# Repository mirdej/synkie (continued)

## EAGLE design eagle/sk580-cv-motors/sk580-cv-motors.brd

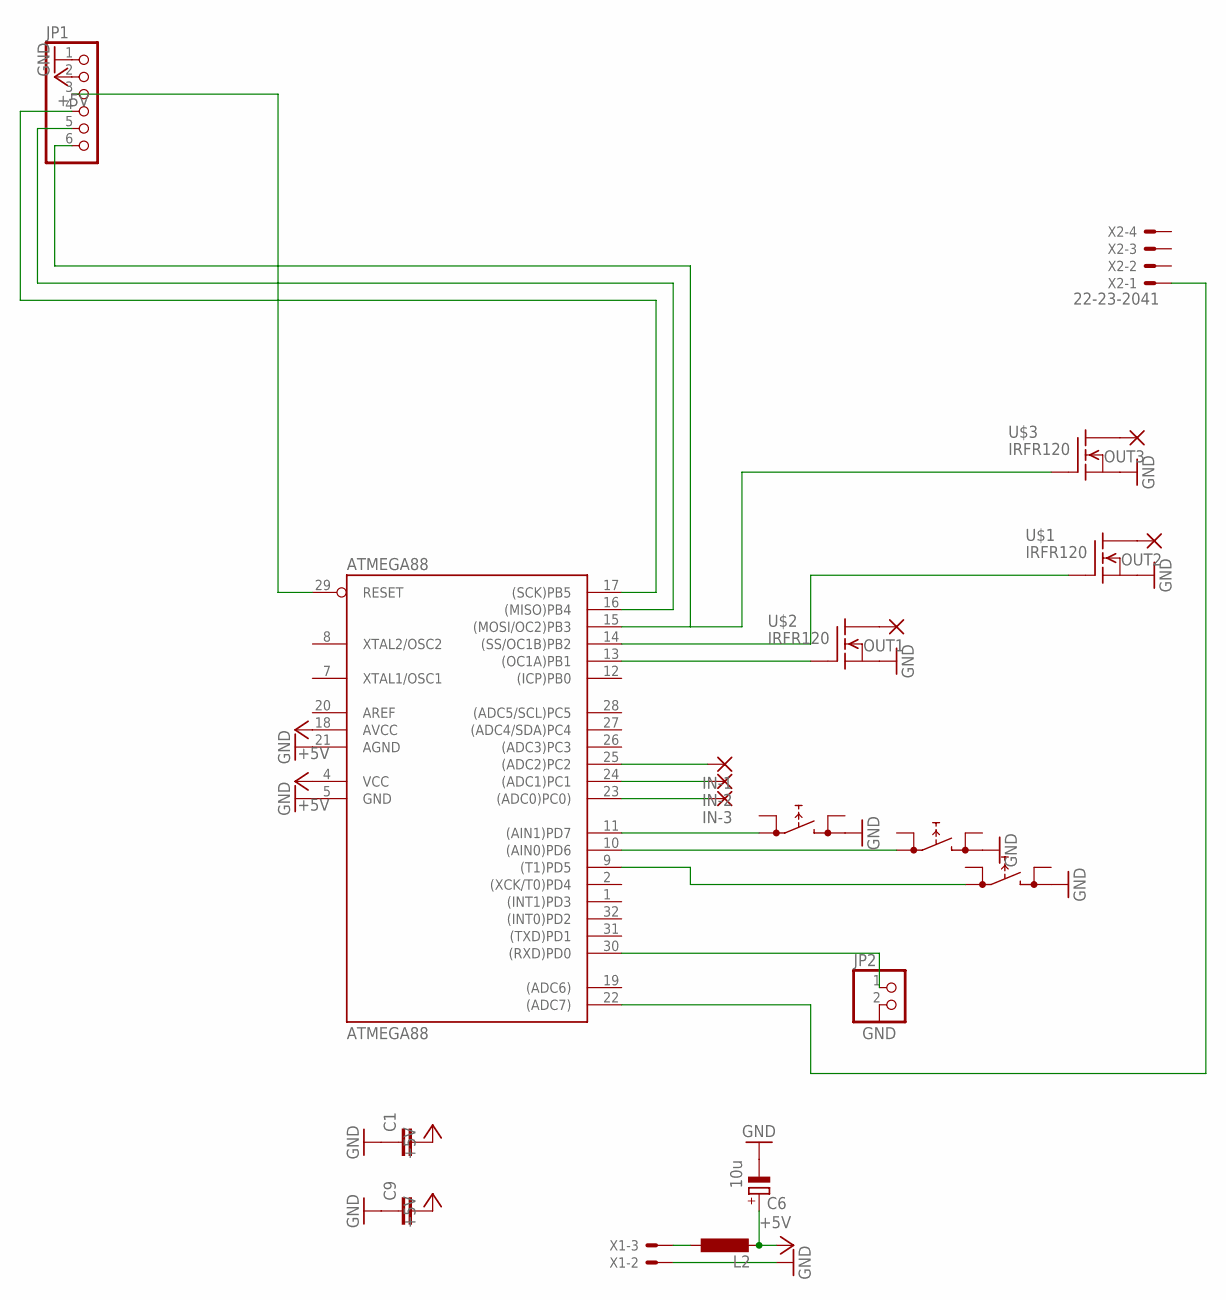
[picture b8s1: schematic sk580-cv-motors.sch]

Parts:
ATMEGA88: ATMEGA88; TQFP32-08
C1, C9: C-EUC0603; C0603
C6: 10u; CT3528
DUB2: PRINTTASTER_SMD; SMD_SWITCH
DUB-1, DUB-3: PRINTTASTER_SMD; SMD_SWITCH
IN-1, IN-2, IN-3: 3,17/1,1
JP1: PINHD-1X6; 1X06
JP2: PINHD-1X2; 1X02
L2: L-EUL5038P; L5038P
OUT1, OUT2, OUT3: 3,17/1,1
U$1, U$2, U$3: IRFR120; DPAK
X1: 22-23-2031
X2: 22-23-2041

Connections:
+5V: ATMEGA88.4 (VCC), ATMEGA88.18 (AVCC), C1.2, C6.+, C9.2, JP1.2, L2.2
AREF: ATMEGA88.20 (AREF)
GND: ATMEGA88.5 (GND), ATMEGA88.21 (AGND), C1.1, C6.-, C9.1, DUB2.BB (1), DUB-1.BB (1), DUB-3.BB (1), JP1.1, JP2.2, U$1.3 (S), U$2.3 (S), U$3.3 (S), X1.2
unnamed: ATMEGA88.29 (RESET), JP1.3
unnamed: ATMEGA88.17 ((SCK)PB5), JP1.4
unnamed: ATMEGA88.16 ((MISO)PB4), JP1.5
unnamed: ATMEGA88.23 ((ADC0)PC0)), IN-3.1
unnamed: ATMEGA88.24 ((ADC1)PC1), IN-2.1
unnamed: ATMEGA88.25 ((ADC2)PC2), IN-1.1
unnamed: ATMEGA88.22 ((ADC7)), X2.1
unnamed: ATMEGA88.30 ((RXD)PD0), JP2.1
unnamed: L2.1, X1.3
unnamed: ATMEGA88.13 ((OC1A)PB1), U$2.1 (G)
unnamed: OUT1.1, U$2.4 (D)
unnamed: ATMEGA88.14 ((SS/OC1B)PB2), U$1.1 (G)
unnamed: OUT2.1, U$1.4 (D)
unnamed: ATMEGA88.15 ((MOSI/OC2)PB3), JP1.6, U$3.1 (G)
unnamed: OUT3.1, U$3.4 (D)
RESET: ATMEGA88.11 ((AIN1)PD7), DUB-1.AA (0)
RESET1: ATMEGA88.10 ((AIN0)PD6), DUB2.AA (0)
RESET2: ATMEGA88.9 ((T1)PD5), DUB-3.AA (0)

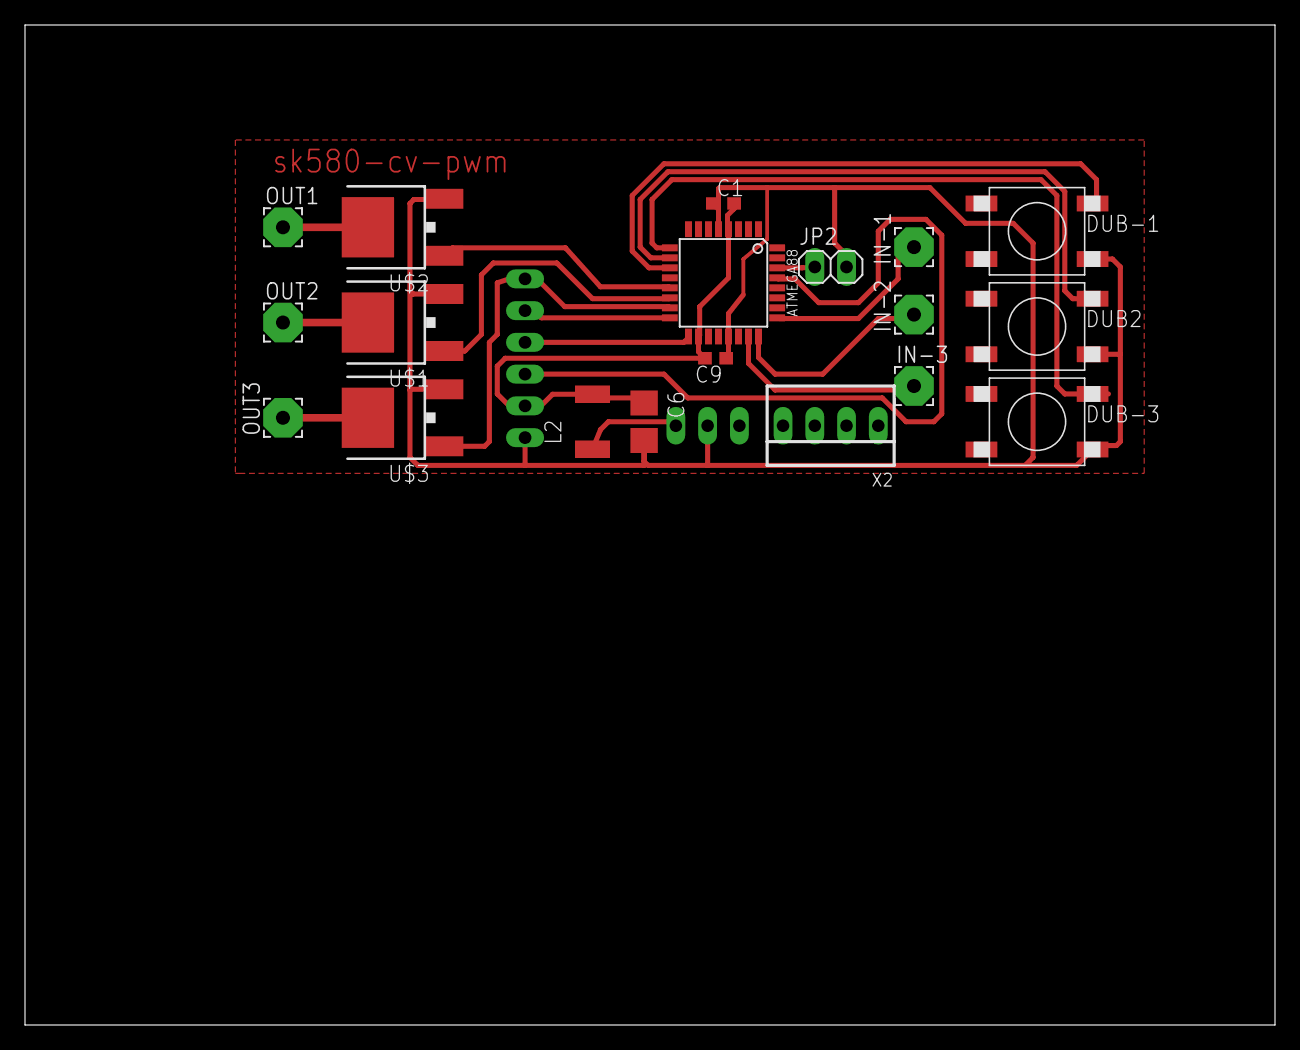
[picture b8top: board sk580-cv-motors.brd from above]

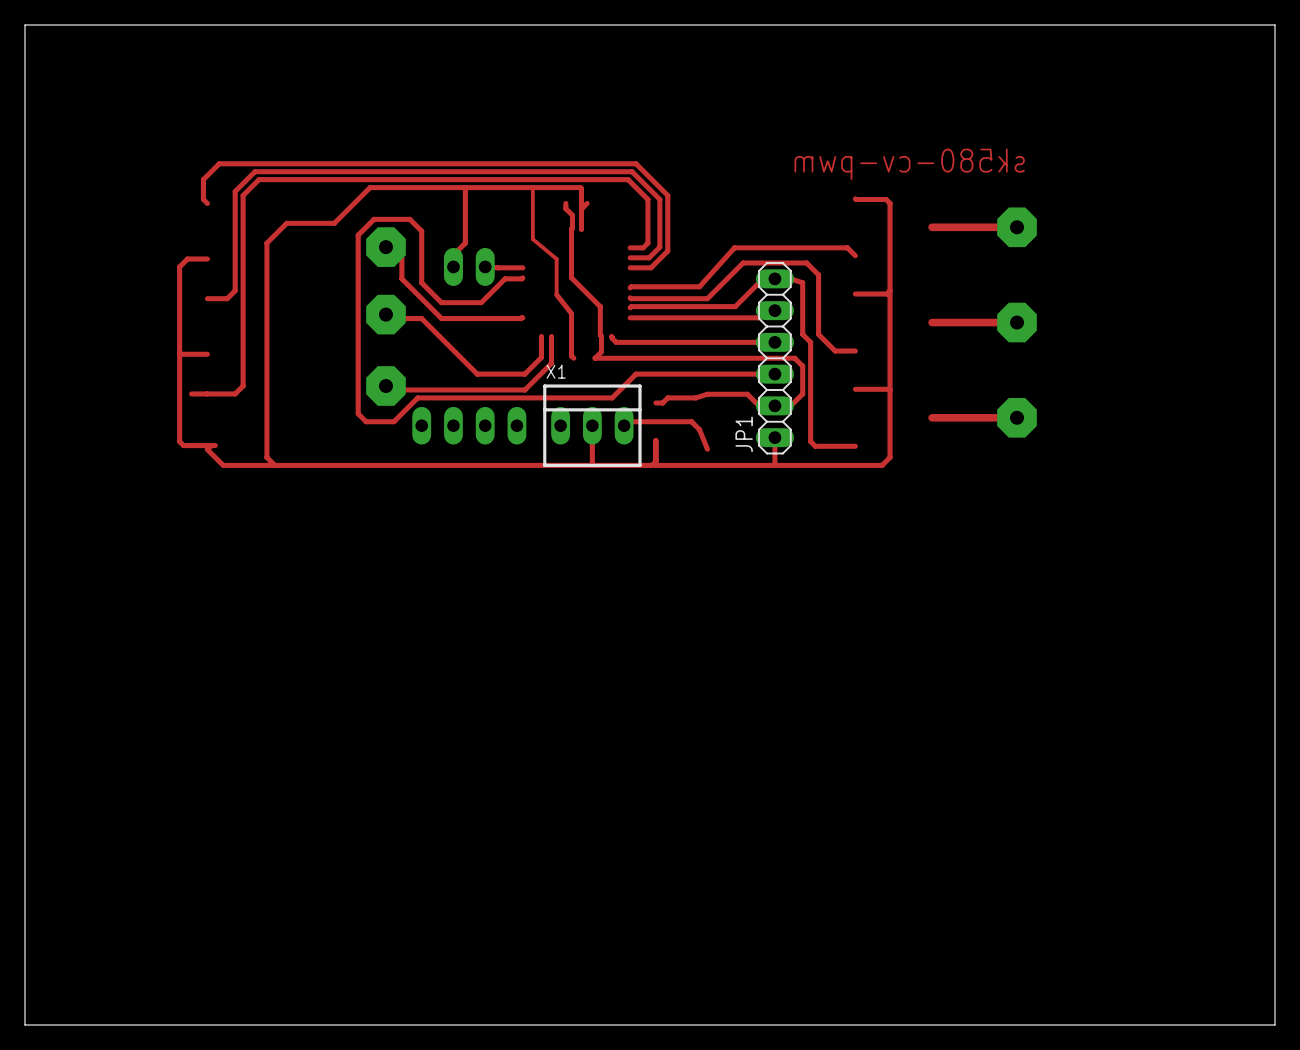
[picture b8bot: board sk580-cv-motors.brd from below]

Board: 2 copper layers, 100.0 x 80.0 mm, 21 parts (2 on the bottom side), 20 nets.
